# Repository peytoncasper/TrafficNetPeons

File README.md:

Setting Up the Web Interface:

1. Ensure Python is installed
2. Ensure Python Dev Tools are installed

	sudo apt-get install python-dev

3. Ensure Python Pip is installed
	
	sudo apt-get install python-pip

4. Install Flask, CORS, and GPIO Zero

	pip install flask
	pip install flask_cors
	pip install gpiozero

5. Run the web interface
	
	python TrafficNet.py

Setting Up UV4l:

http://www.instructables.com/id/Raspberry-Pi-Video-Streaming/?ALLSTEPS

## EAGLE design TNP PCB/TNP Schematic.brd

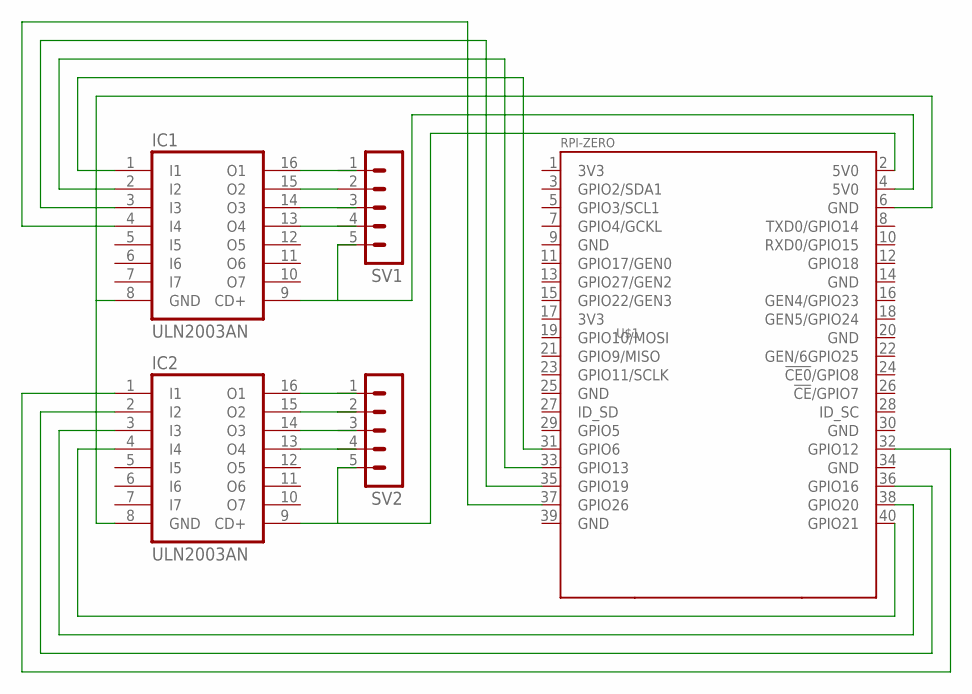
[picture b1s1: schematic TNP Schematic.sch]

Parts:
IC1, IC2: ULN2003AN; DIL16
SV1, SV2: MA05-1
U$1: RPI-ZERO; RASPBERRYPI_BASTELSTUBE_V13_RASPI_BOARD_B+_FULL

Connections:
5V0@1: IC2.9 (CD+), SV2.5, U$1.2 (5V0)
5V0@2: IC1.9 (CD+), SV1.5, U$1.4 (5V0)
GND@8: IC1.8 (GND), IC2.8 (GND), U$1.6 (GND)
unnamed: IC1.16 (O1), SV1.1
unnamed: IC1.15 (O2), SV1.2
unnamed: IC1.14 (O3), SV1.3
unnamed: IC1.13 (O4), SV1.4
unnamed: IC2.16 (O1), SV2.1
unnamed: IC2.15 (O2), SV2.2
unnamed: IC2.14 (O3), SV2.3
unnamed: IC2.13 (O4), SV2.4
unnamed: IC2.4 (I4), U$1.40 (GPIO21)
unnamed: IC2.3 (I3), U$1.38 (GPIO20)
unnamed: IC2.2 (I2), U$1.36 (GPIO16)
unnamed: IC1.1 (I1), U$1.31 (GPIO6)
unnamed: IC1.2 (I2), U$1.33 (GPIO13)
unnamed: IC1.3 (I3), U$1.35 (GPIO19)
unnamed: IC1.4 (I4), U$1.37 (GPIO26)
unnamed: IC2.1 (I1), U$1.32 (GPIO12)

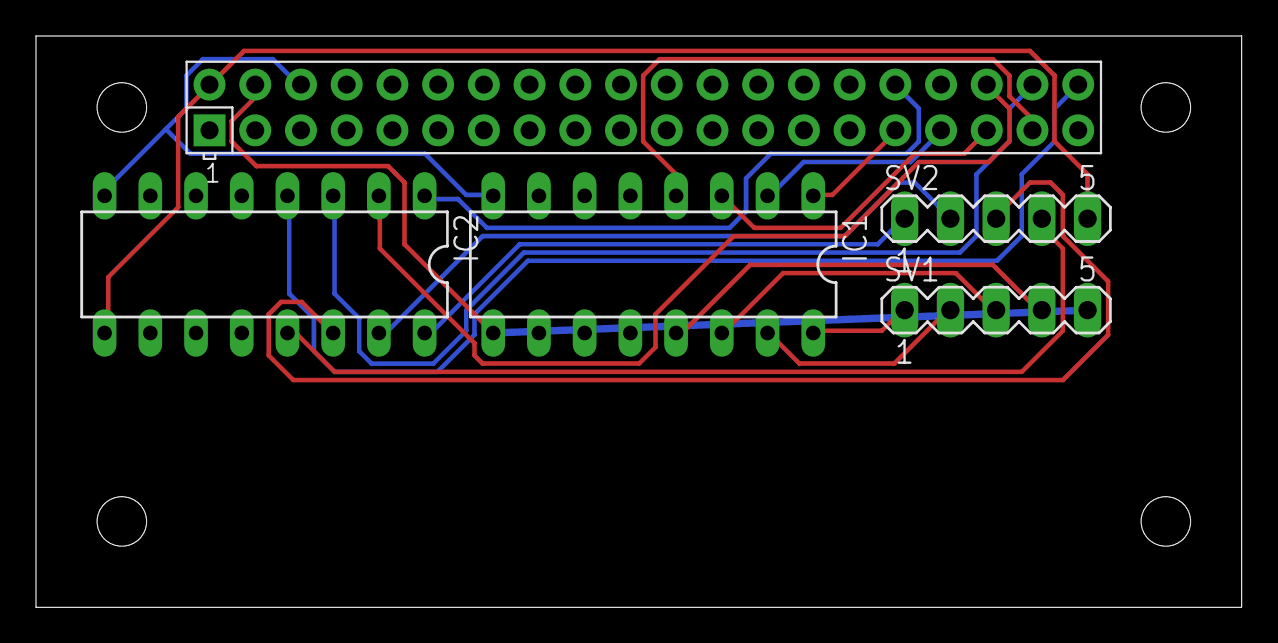
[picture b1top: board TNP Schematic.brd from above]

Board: 2 copper layers, 67.0 x 31.7 mm, 5 parts (0 on the bottom side), 19 nets.

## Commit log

2016-03-11 Added files via upload
2016-03-11 Added the compiled system requirements and the first 3 sections
2016-03-11 Updated PDF to include acceptance
2016-03-25 Added in Stepper Motor Control and merge
2016-04-06 Added in the ADS
2016-04-06 Camera layer updated - Jose
2016-04-06 Create base_station_layer_subsystems
2016-04-07 Updated changes to Camera layer - Jose
2016-04-07 Update system_overview.tex
    Updated System overview
    Updated camera layer
    Updated web interface
2016-04-07 Update data_flow.tex
    Updated data flow
2016-04-07 Update system_overview.tex
    Wireless communication layer updated
2016-04-07 Update system_overview.tex
    Done my part still need diagram
2016-04-07 Added files via upload
    layers image added
2016-04-08 Updated to include the introduction
2016-04-08 Updated to include team info
2016-04-09 Update base_station_layer_subsystems
2016-04-11 Moved the ads diagrams folder in to the images folder
2016-04-15 Updates for the keyboard control which include foward, back, left, and right control
2016-06-24 Added intial Web interface
2016-06-24 Added Login Page
2016-06-24 Deleted IP Address Input
2016-06-24 Deleted Forget Password/Register options
2016-07-08 Updated to include login popup window.
2016-07-14 Syncing web interface
2016-07-15 Added the vlc loading
2016-07-15 Updates to error handling for username, password, ip
2016-07-18 Updates for web interface
2016-08-07 Added in DDS
2016-08-08 Camera Layer
2016-08-09 Added updates for the web ui
2016-08-09 Updated motor control code
2016-08-09 Added bounding logic for the motor control
2016-08-09 Added Introduction
2016-08-09 Enabled motor control
2016-08-09 Updated sleep settings and addded the step right ajax call
2016-08-09 Upated motor pins
2016-08-09 Updates to add config horizontal and vertical settings
2016-08-09 Binded in the other buttons
2016-08-09 Initial start for orientation label logic
2016-08-10 updated data_flow
2016-08-10 updated system_overview
2016-08-10 Updated Camera Layer
2016-08-10 dataflow and layers diagram uploaded
2016-08-17 Create Presentation Video
2016-08-26 Syncing without large files
